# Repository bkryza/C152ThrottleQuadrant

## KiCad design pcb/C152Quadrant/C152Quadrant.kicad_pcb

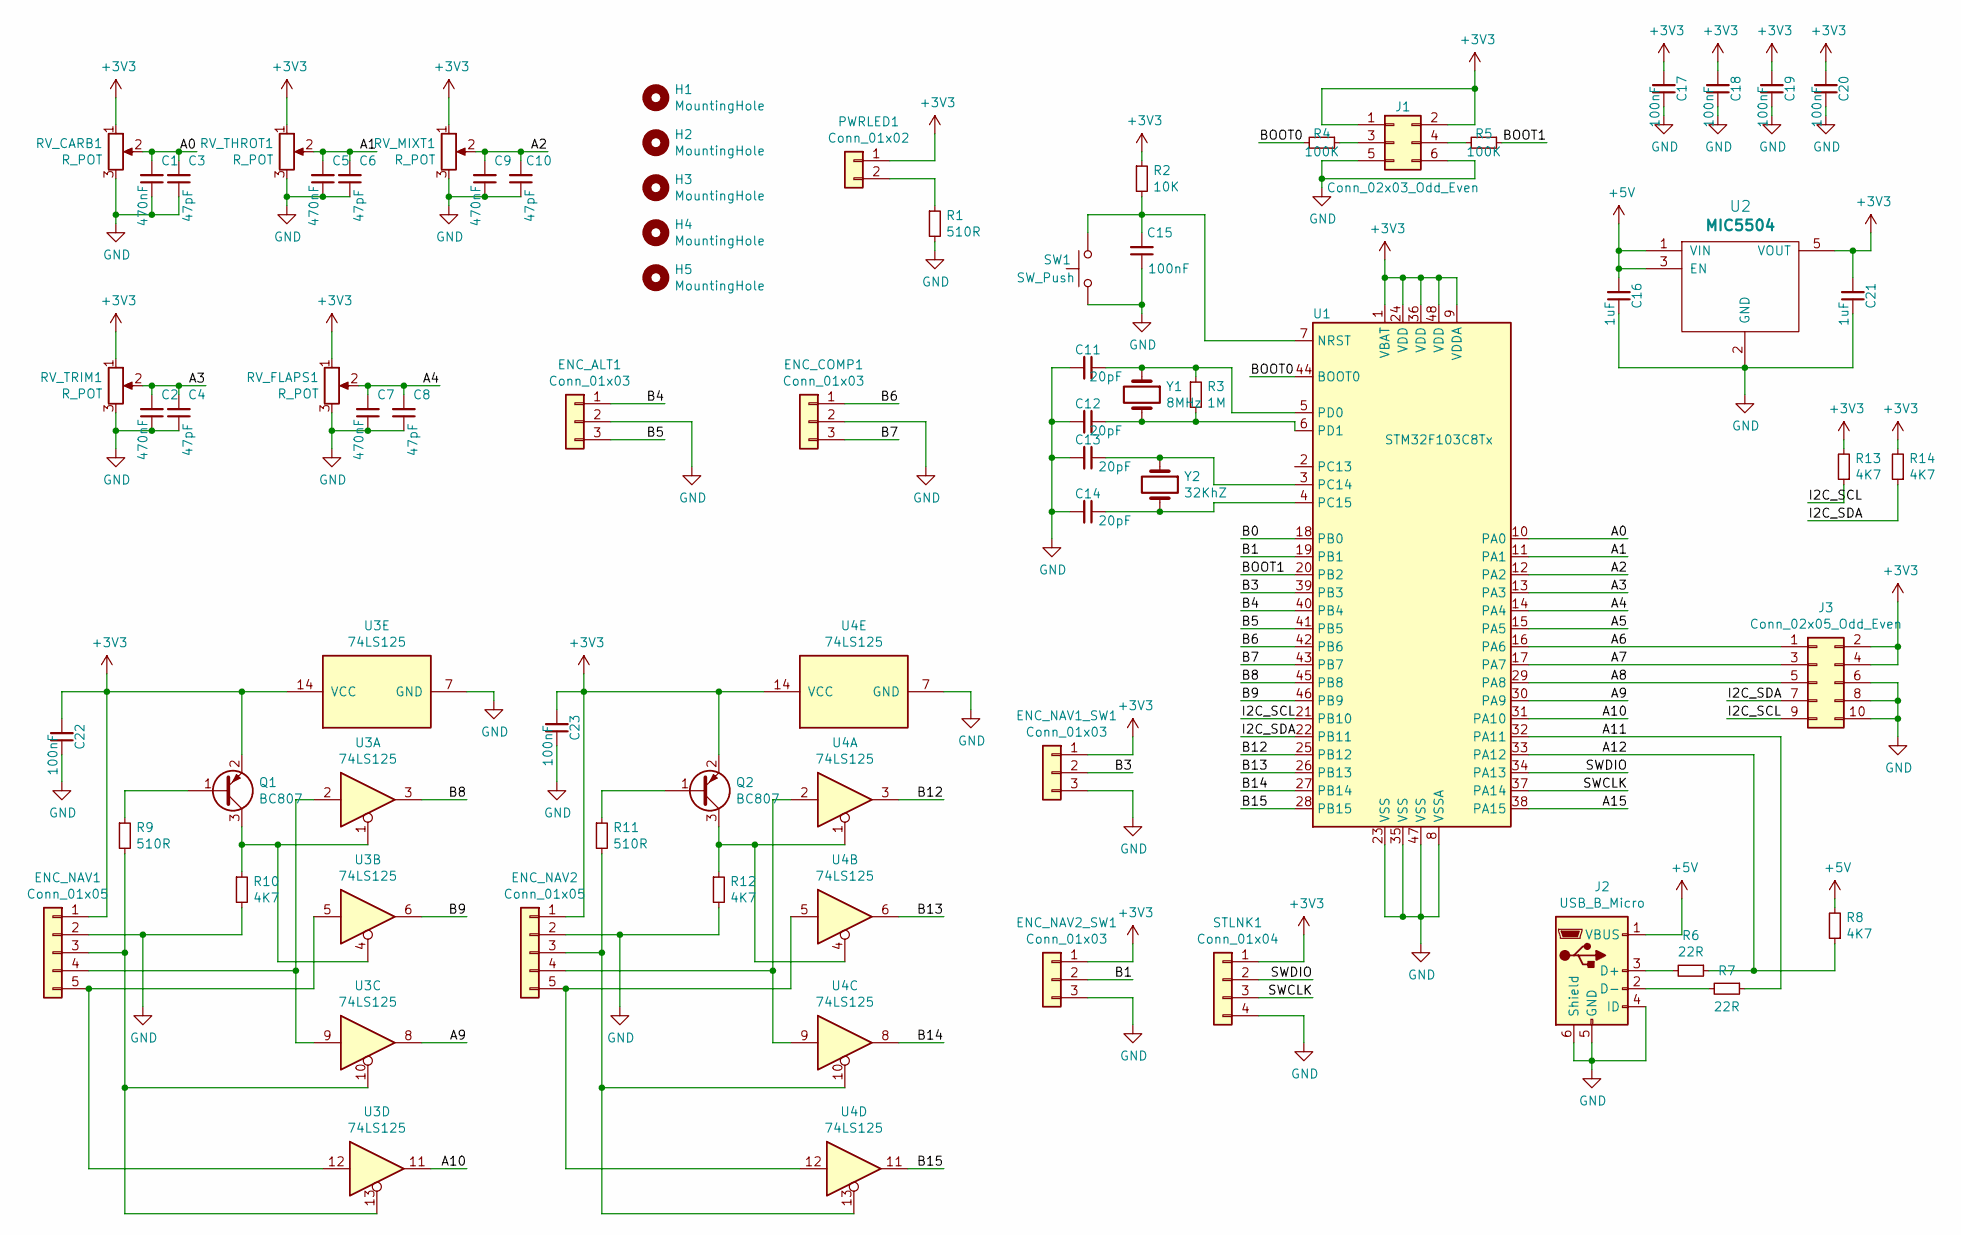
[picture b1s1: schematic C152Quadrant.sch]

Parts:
C1, C2, C5, C7, C9: 470nF; C_0603_1608Metric_Pad1.08x0.95mm_HandSolder
C3, C4, C6, C8, C10: 47pF; C_0603_1608Metric_Pad1.08x0.95mm_HandSolder
C11, C12, C13, C14: 20pF; C_0603_1608Metric_Pad1.08x0.95mm_HandSolder
C15, C17, C18, C19, C20, C22, C23: 100nF; C_0603_1608Metric_Pad1.08x0.95mm_HandSolder
C16, C21: 1uF; C_1206_3216Metric_Pad1.33x1.80mm_HandSolder
ENC_ALT1: Conn_01x03; PinHeader_1x03_P2.54mm_Vertical
ENC_COMP1: Conn_01x03; PinHeader_1x03_P2.54mm_Vertical
ENC_NAV1, ENC_NAV2: Conn_01x05; PinHeader_1x05_P2.54mm_Vertical
ENC_NAV1_SW1, ENC_NAV2_SW1: Conn_01x03; PinHeader_1x03_P2.54mm_Vertical
H1, H2, H3, H4, H5: MountingHole; MountingHole_3.2mm_M3_DIN965_Pad
J1: Conn_02x03_Odd_Even; PinHeader_2x03_P2.54mm_Vertical
J2: USB_B_Micro; USB_Mini-B_Wuerth_65100516121_Horizontal
J3: Conn_02x05_Odd_Even; PinSocket_2x05_P2.54mm_Vertical
PWRLED1: Conn_01x02; PinHeader_1x02_P2.54mm_Vertical
Q1, Q2: BC807; SOT-23
R1, R9, R11: 510R; R_0603_1608Metric_Pad0.98x0.95mm_HandSolder
R2: 10K; R_0603_1608Metric_Pad0.98x0.95mm_HandSolder
R3: 1M; R_0603_1608Metric_Pad0.98x0.95mm_HandSolder
R4, R5: 100K; R_0603_1608Metric_Pad0.98x0.95mm_HandSolder
R6, R7: 22R; R_0603_1608Metric_Pad0.98x0.95mm_HandSolder
R8, R10, R12, R13, R14: 4K7; R_0603_1608Metric_Pad0.98x0.95mm_HandSolder
RV_CARB1: R_POT; RS6011SY
RV_FLAPS1: R_POT; PinHeader_1x03_P2.54mm_Vertical
RV_MIXT1: R_POT; RS6011SY
RV_THROT1: R_POT; RS6011SY
RV_TRIM1: R_POT; PinHeader_1x03_P2.54mm_Vertical
STLNK1: Conn_01x04; PinHeader_1x04_P2.54mm_Vertical
SW1: SW_Push; SW_SPST_EVPBF
U1: STM32F103C8Tx; LQFP-48_7x7mm_P0.5mm
U2: MIC5504; SOT-23-5_HandSoldering
U3, U4: 74LS125; SOIC-14_3.9x8.7mm_P1.27mm
Y1: 8MHz; Crystal_HC49-4H_Vertical
Y2: 32KhZ; Crystal_DS15_D1.5mm_L5.0mm_Horizontal_1EP_style1

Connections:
+3V3: C17.2, C18.2, C19.2, C20.2, C21.2, C22.2, C23.2, ENC_NAV1.1, ENC_NAV1_SW1.1, ENC_NAV2.1, ENC_NAV2_SW1.1, J1.1, J1.2, J3.2, J3.4, PWRLED1.1, Q1.2 (E), Q2.2 (E), R2.1, R13.2, R14.2, RV_CARB1.1, RV_FLAPS1.1, RV_MIXT1.1, RV_THROT1.1, RV_TRIM1.1, STLNK1.1, U1.1 (VBAT), U1.9 (VDDA), U1.24 (VDD), U1.36 (VDD), U1.48 (VDD), U2.5 (VOUT), U3.14 (VCC), U4.14 (VCC)
+5V: C16.2, J2.1 (VBUS), R8.2, U2.1 (VIN), U2.3 (EN)
/A0: C1.2, C3.2, RV_CARB1.2, U1.10 (PA0)
/A1: C5.2, C6.2, RV_THROT1.2, U1.11 (PA1)
/A2: C9.2, C10.2, RV_MIXT1.2, U1.12 (PA2)
/A3: C2.2, C4.2, RV_TRIM1.2, U1.13 (PA3)
/A4: C7.2, C8.2, RV_FLAPS1.2, U1.14 (PA4)
/A5: U1.15 (PA5)
/A6: J3.1, U1.16 (PA6)
/A7: J3.3, U1.17 (PA7)
/A8: J3.5, U1.29 (PA8)
/A9: U1.30 (PA9), U3.8
/A10: U1.31 (PA10), U3.11
/A11: R7.1, U1.32 (PA11)
/A12: R6.1, R8.1, U1.33 (PA12)
/A15: U1.38 (PA15)
/B0: U1.18 (PB0)
/B1: ENC_NAV2_SW1.2, U1.19 (PB1)
/B3: ENC_NAV1_SW1.2, U1.39 (PB3)
/B4: ENC_ALT1.1, U1.40 (PB4)
/B5: ENC_ALT1.3, U1.41 (PB5)
/B6: ENC_COMP1.1, U1.42 (PB6)
/B7: ENC_COMP1.3, U1.43 (PB7)
/B8: U1.45 (PB8), U3.3
/B9: U1.46 (PB9), U3.6
/B12: U1.25 (PB12), U4.3
/B13: U1.26 (PB13), U4.6
/B14: U1.27 (PB14), U4.8
/B15: U1.28 (PB15), U4.11
/BOOT0: R4.2, U1.44 (BOOT0)
/BOOT1: R5.1, U1.20 (PB2)
/I2C_SCL: J3.9, R13.1, U1.21 (PB10)
/I2C_SDA: J3.7, R14.1, U1.22 (PB11)
/SWCLK: STLNK1.3, U1.37 (PA14)
/SWDIO: STLNK1.2, U1.34 (PA13)
GND: C1.1, C2.1, C3.1, C4.1, C5.1, C6.1, C7.1, C8.1, C9.1, C10.1, C11.2, C12.2, C13.2, C14.2, C15.1, C16.1, C17.1, C18.1, C19.1, C20.1, C21.1, C22.1, C23.1, ENC_ALT1.2, ENC_COMP1.2, ENC_NAV1.2, ENC_NAV1_SW1.3, ENC_NAV2.2, ENC_NAV2_SW1.3, J1.5, J1.6, J2.4 (ID), J2.5 (GND), J2.6 (Shield), J3.6, J3.8, J3.10, R1.2, R10.2, R12.2, RV_CARB1.3, RV_FLAPS1.3, RV_MIXT1.3, RV_THROT1.3, RV_TRIM1.3, STLNK1.4, SW1.1, U1.8 (VSSA), U1.23 (VSS), U1.35 (VSS), U1.47 (VSS), U2.2 (GND), U3.7 (GND), U4.7 (GND)
unnamed: C11.1, R3.1, U1.5 (PD0), Y1.1
unnamed: C12.1, R3.2, U1.6 (PD1), Y1.2
unnamed: C13.1, U1.3 (PC14), Y2.1
unnamed: C14.1, U1.4 (PC15), Y2.2
unnamed: C15.2, R2.2, SW1.2, U1.7 (NRST)
unnamed: ENC_NAV1.3, R9.2, U3.10, U3.13
unnamed: ENC_NAV1.4, U3.2, U3.9
unnamed: ENC_NAV1.5, U3.5, U3.12
unnamed: ENC_NAV2.3, R11.2, U4.10, U4.13
unnamed: ENC_NAV2.4, U4.2, U4.9
unnamed: ENC_NAV2.5, U4.5, U4.12
unnamed: J1.3, R4.1
unnamed: J1.4, R5.2
unnamed: J2.2 (D-), R7.2
unnamed: J2.3 (D+), R6.2
unnamed: PWRLED1.2, R1.1
unnamed: Q1.1 (B), R9.1
unnamed: Q1.3 (C), R10.1, U3.1, U3.4
unnamed: Q2.1 (B), R11.1
unnamed: Q2.3 (C), R12.1, U4.1, U4.4

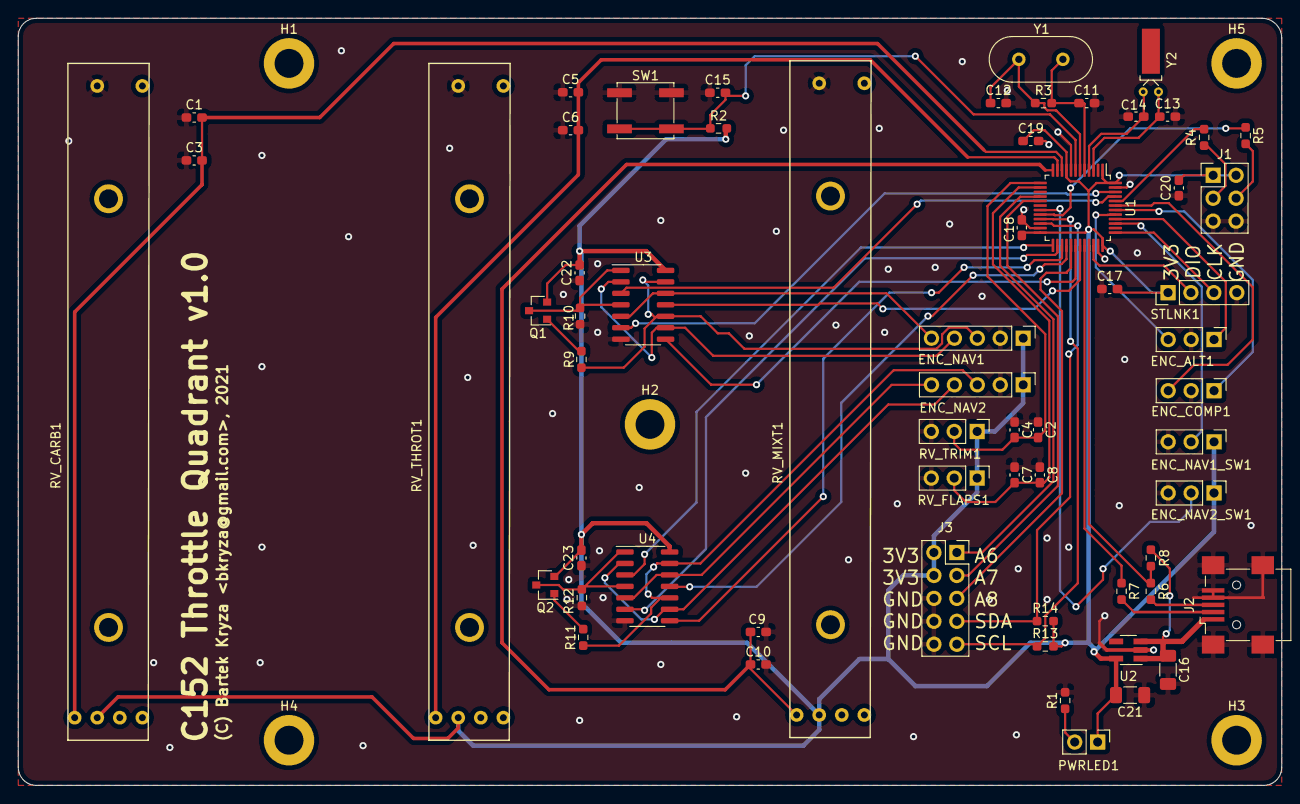
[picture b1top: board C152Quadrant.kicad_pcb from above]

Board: 2 copper layers, 140.0 x 85.0 mm, 67 parts (0 on the bottom side), 53 nets.

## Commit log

2021-05-19 Added PCB gerber files
2021-05-30 First version
2021-06-03 New version
